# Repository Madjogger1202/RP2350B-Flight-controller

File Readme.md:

# RP2350B-Flight-controller  

> Ultra-compact flight controller for mini quadcopters, based on **RP2350B** MCU.  
> Board size: **30.5 × 39.8 mm**, yet includes IMU, radio module, motor drivers, and full USB power support.  

---

## Key Features  
- **MCU:** RP2350B (dual-core, PIO, USB device)  
- **IMU:** LSM6DS3 (accelerometer + gyroscope, SPI connection)  
- **Radio module:** NRF24L01 + RFX2401C PA/LNA amplifier  
- **Motors:** 4× brushed DC motors (up to 5 A per channel, short peak)  
- **USB-powered flight possible** (low-current motors, enough supply over USB)  
- **Additional expansion pins** (GPIO3–16 + SWD) for sensors, debugging, or add-ons  

---

## Pin Mapping  

### IMU (LSM6DS3) — SPI2  
| RP2350B GPIO | Signal | Notes |
|--------------|--------|-------|
| GPIO19 | SPI2_MISO | Sensor data out |
| GPIO22 | SPI2_MOSI | Sensor data in |
| GPIO23 | SPI2_SCK  | SPI clock |
| GPIO20 | IMU_INT1  | Interrupt 1 |
| GPIO21 | IMU_INT2  | Interrupt 2 |

---

### Radio Module (NRF24L01 + RFX2401C)  
| RP2350B GPIO | Signal | Notes |
|--------------|--------|-------|
| GPIO28 | SPI_MOSI | Shared SPI bus |
| GPIO36 | SPI_MISO | Shared SPI bus |
| GPIO37 | SPI_SCK  | Shared SPI bus |
| GPIO30 | NRF_CS   | Chip select |
| GPIO31 | NRF_CE   | Enable |
| GPIO32 | NRF_IRQ  | Interrupt |

---

### Motors  
| RP2350B GPIO | Output | Notes |
|--------------|--------|-------|
| GPIO45 | Motor_1 | Brushed motor driver |
| GPIO46 | Motor_2 | Brushed motor driver |
| GPIO47 | Motor_3 | Brushed motor driver |
| GPIO48 | Motor_4 | Brushed motor driver |
| GPIO49 | Motor_current | Current sense |
| GPIO52 | Motor_voltage | Battery/rail voltage sense |

---

### LEDs  
| RP2350B GPIO | Signal | Notes |
|--------------|--------|-------|
| GPIO17 | LED1 | Status LED |
| GPIO18 | LED2 | Status LED |

---

### Debug / Expansion  
- **SWD interface** exposed for programming/debugging  
- **GPIO3–16** free for custom extensions (I²C, UART, SPI, PWM, ADC etc.)  

---

## Power  
- Powered from **USB** or external battery  
- USB can sustain hover/low-thrust operation with small coreless motors  
- Onboard regulation for MCU, IMU, radio, and motor supply  

---

## Use Case  
- Designed for **tiny brushed quadcopters** and robotics experiments  
- Combines **motion sensing, wireless control, and motor drivers** in one small board  
- Fits into custom drone frames without extra breakout boards  

---

## Quick Start  
1. Connect via **USB-C** for firmware flashing and testing.  
2. Flash firmware (e.g. custom flight stack on RP2350B).  
3. Connect brushed motors to outputs GPIO45–48.  
4. Pair radio link via NRF24L01 (with RFX2401C amp).  
5. Power from USB for tests, or from LiPo for flight.  

---

## Notes  
- Motor channels rated for **5 A peak per motor** (coreless brushed).  
- Ensure airflow for heat dissipation at higher loads.  
- Expansion pins allow integration of GPS, barometer, or additional sensors.  

---

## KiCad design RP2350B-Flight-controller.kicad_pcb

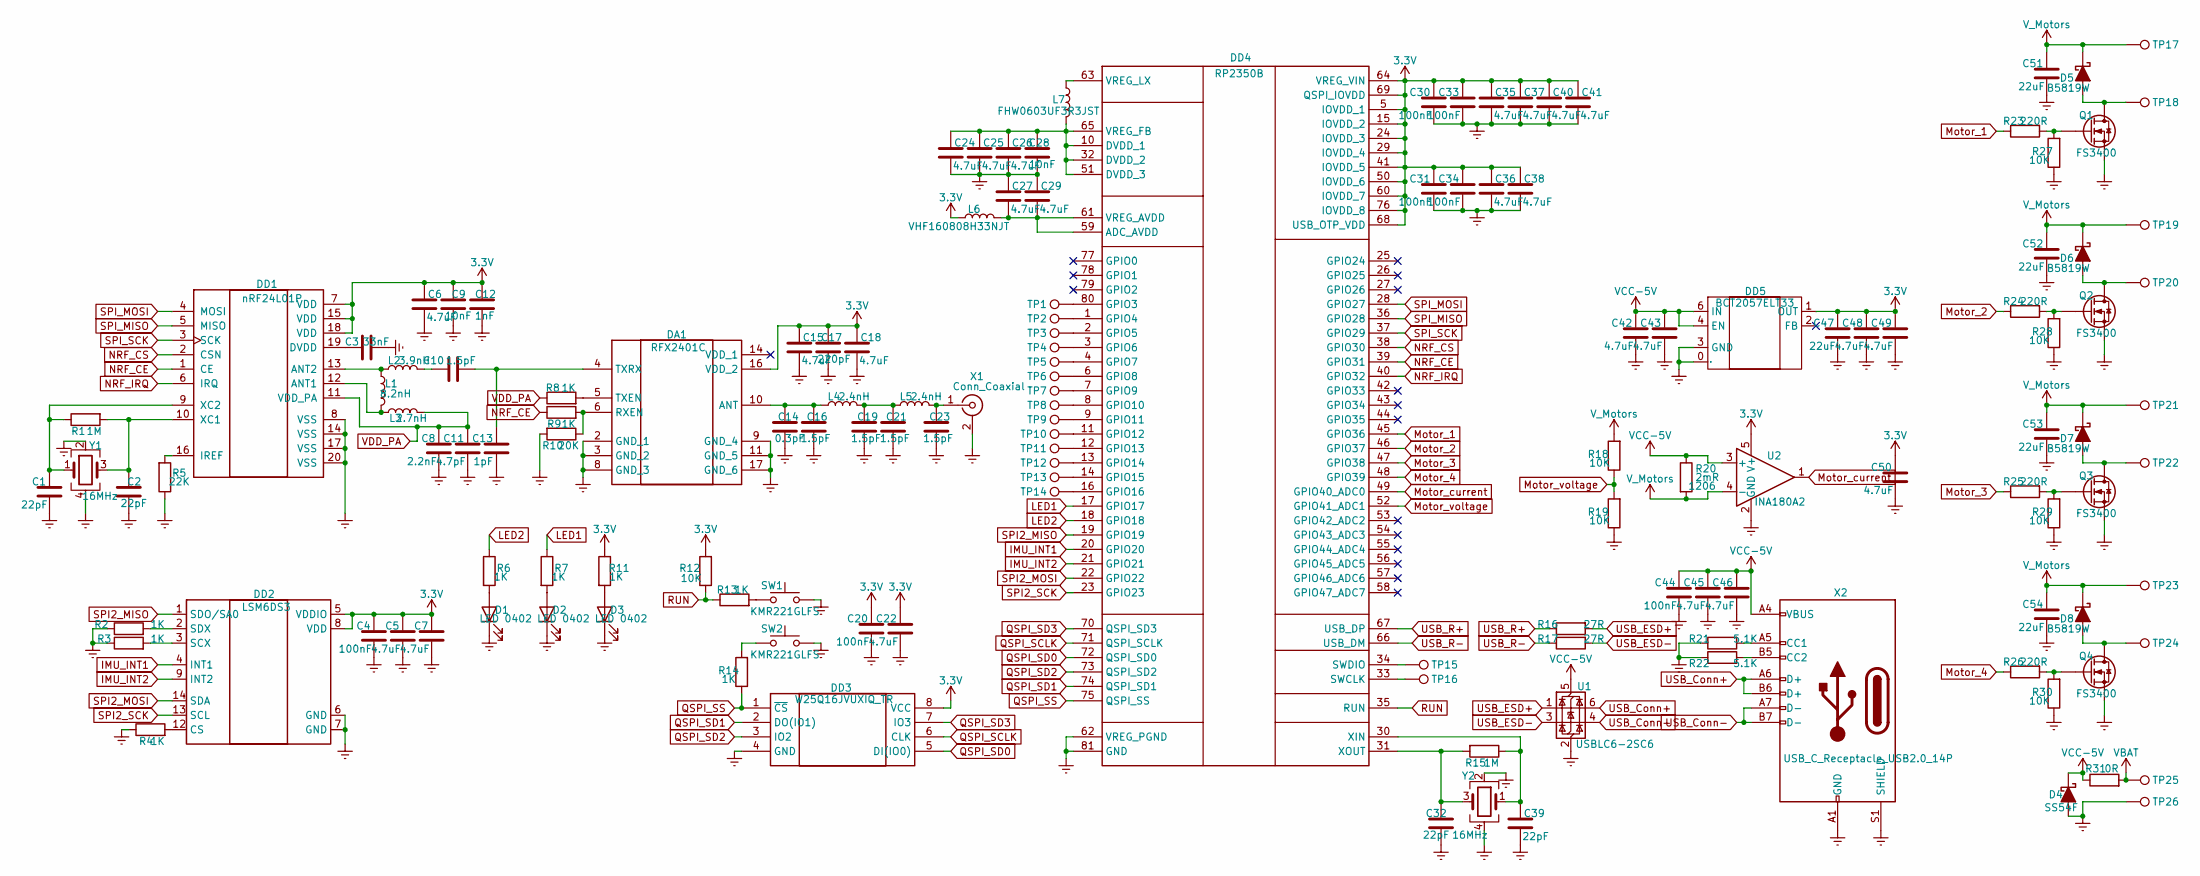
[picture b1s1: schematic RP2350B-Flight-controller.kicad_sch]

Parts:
C1, C2, C32, C39: 22pF; C_0201_0603Metric
C3: 33nF; C_0201_0603Metric
C4, C20, C30, C31, C33, C34, C44: 100nF; C_0201_0603Metric
C5, C6, C7, C15, C18, C22, C24, C25, C26, C27, C29, C35, C36, C37, C38, C40, C41, C42, C43, C45, C46, C48, C49, C50: 4.7uF; C_0201_0603Metric
C8: 2.2nF; C_0201_0603Metric
C9, C28: 10nF; C_0201_0603Metric
C10, C16, C19, C21, C23: 1.5pF; C_0201_0603Metric
C11: 4.7pF; C_0201_0603Metric
C12: 1nF; C_0201_0603Metric
C13: 1pF; C_0201_0603Metric
C14: 0.3pF; C_0201_0603Metric
C17: 220pF; C_0201_0603Metric
C47, C51, C52, C53, C54: 22uF; C_0402_1005Metric
D1, D2, D3: LED 0402; LED_0402_1005Metric
D4: SS54F; D_SMAFL
D5, D6, D7, D8: B5819W; D_SOD-123
DA1: RFX2401C; Manufacturer_Part_Number RFX2401C; Mouser Part Number 477-RFX2401C
DD1: nRF24L01P; QFN-20-1EP_4x4mm_P0.5mm_EP2.5x2.5mm
DD2: LSM6DS3; LGA-14_3x2.5mm_P0.5mm_LayoutBorder3x4y
DD3: W25Q16JVUXIQ_TR; W25Q16JVUXIQ; Manufacturer_Part_Number W25Q16JVUXIQ TR; Mouser Part Number 454-W25Q16JVUXIQTR
DD4: RP2350B; QFN40P1000X1000X90-81N-D; Manufacturer_Part_Number RP2350B
DD5: BCT2057ELT33; BCT2057ELTAJ; Manufacturer Part BCT2057ELTAJ-TR; LCSC Part Name 1A, 低 dropout 线性稳压器
L1: 8.2nH; L_0201_0603Metric
L2: 3.9nH; L_0201_0603Metric
L3: 2.7nH; L_0201_0603Metric
L4, L5: 2.4nH; L_0201_0603Metric
L6: VHF160808H33NJT; L_0603_1608Metric
L7: FHW0603UF3R3JST; L_0603_1608Metric
Q1, Q2, Q3, Q4: FS3400; SOT-23
R1, R15: 1M; R_0201_0603Metric
R2, R3, R4, R6, R7, R8, R9, R11, R13, R14: 1K; R_0201_0603Metric
R5: 22K; R_0201_0603Metric
R10: 20K; R_0201_0603Metric
R12, R18, R19, R27, R28, R29, R30: 10K; R_0201_0603Metric
R16, R17: 27R; R_0201_0603Metric
R20: 2mR; R_1206_3216Metric
R21, R22: 5.1K; R_0201_0603Metric
R23, R24, R25, R26: 220R; R_0201_0603Metric
R31: 0R; R_0805_2012Metric
SW1, SW2: KMR221GLFS; SW_SPST_PTS810
TP1, TP2, TP3, TP4, TP5, TP6, TP7, TP8, TP9, TP10, TP11, TP12, TP13, TP14, TP15, TP16: TestPoint; TestPoint_Pad_D1.0mm
TP17, TP18, TP19, TP20, TP21, TP22, TP23, TP24, TP25, TP26: TestPoint; TestPoint_Pad_D1.5mm
U1: USBLC6-2SC6; SOT-23-6
U2: INA180A2; SOT-23-5
X1: Conn_Coaxial; U.FL_Molex_MCRF_73412-0110_Vertical
X2: USB_C_Receptacle_USB2.0_14P; USB_C_Receptacle_GCT_USB4105-xx-A_16P_TopMnt_Horizontal
Y1, Y2: 16MHz; Crystal_SMD_3225-4Pin_3.2x2.5mm

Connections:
3.3V: C4.1, C5.1, C6.1, C7.1, C9.1, C12.1, C15.1, C17.1, C18.1, C20.1, C22.1, C30.1, C31.1, C33.1, C34.1, C35.1, C36.1, C37.1, C38.1, C40.1, C41.1, C47.1, C48.1, C49.1, C50.1, DA1.16 (VDD_2), DD1.7 (VDD), DD1.15 (VDD), DD1.18 (VDD), DD2.5 (VDDIO), DD2.8 (VDD), DD3.8 (VCC), DD4.5 (IOVDD_1), DD4.15 (IOVDD_2), DD4.24 (IOVDD_3), DD4.29 (IOVDD_4), DD4.41 (IOVDD_5), DD4.50 (IOVDD_6), DD4.60 (IOVDD_7), DD4.64 (VREG_VIN), DD4.68 (USB_OTP_VDD), DD4.69 (QSPI_IOVDD), DD4.76 (IOVDD_8), DD5.1 (OUT), L6.1, R11.1, R12.2, U2.5 (V+)
Earth: C1.2, C2.2, C3.2, C4.2, C5.2, C6.2, C7.2, C8.2, C9.2, C11.2, C12.2, C13.2, C14.2, C15.2, C16.2, C17.2, C18.2, C19.2, C20.2, C21.2, C22.2, C23.2, C24.2, C25.2, C26.2, C27.1, C28.2, C29.1, C30.2, C31.2, C32.2, C33.2, C34.2, C35.2, C36.2, C37.2, C38.2, C39.2, C40.2, C41.2, C42.2, C43.2, C44.2, C45.2, C46.2, C47.2, C48.2, C49.2, C50.2, C51.2, C52.2, C53.2, C54.2, D1.1 (K), D2.1 (K), D3.1 (K), D4.2 (A), DA1.2 (GND_1), DA1.3 (GND_2), DA1.8 (GND_3), DA1.9 (GND_4), DA1.11 (GND_5), DA1.17 (GND_6), DD1.8 (VSS), DD1.14 (VSS), DD1.17 (VSS), DD1.20 (VSS), DD1.21 (PAD), DD2.6 (GND), DD2.7 (GND), DD3.4 (GND), DD4.62 (VREG_PGND), DD4.81 (GND), DD5.0 (EP), DD5.3 (GND), Q1.2 (S), Q2.2 (S), Q3.2 (S), Q4.2 (S), R2.1, R3.1, R4.1, R5.1, R10.2, R19.1, R21.1, R22.1, R27.1, R28.1, R29.1, R30.1, SW1.1, SW2.1, TP26.1, U1.2 (GND), U2.2 (GND), X1.2 (Ext), X2.A1 (GND), X2.A12 (GND), X2.B1 (GND), X2.B12 (GND), X2.S1 (SHIELD), Y1.2, Y1.4, Y2.2, Y2.4
IMU_INT1: DD2.4 (INT1), DD4.20 (GPIO20)
IMU_INT2: DD2.9 (INT2), DD4.21 (GPIO21)
LED1: DD4.17 (GPIO17), R7.1
LED2: DD4.18 (GPIO18), R6.1
Motor_1: DD4.45 (GPIO36), R23.1
Motor_2: DD4.46 (GPIO37), R24.1
Motor_3: DD4.47 (GPIO38), R25.1
Motor_4: DD4.48 (GPIO39), R26.1
Motor_current: DD4.49 (GPIO40_ADC0), U2.1
Motor_voltage: DD4.52 (GPIO41_ADC1), R18.1, R19.2
NRF_CE: DD1.1 (CE), DD4.39 (GPIO31), R9.1
NRF_CS: DD1.2 (CSN), DD4.38 (GPIO30)
NRF_IRQ: DD1.6 (IRQ), DD4.40 (GPIO32)
unnamed: C10.1, L2.2
unnamed: C19.1, C21.1, L4.2, L5.1
unnamed: D1.2 (A), R6.2
unnamed: D2.2 (A), R7.2
unnamed: D3.2 (A), R11.2
unnamed: D5.2 (A), Q1.3 (D), TP18.1
unnamed: D6.2 (A), Q2.3 (D), TP20.1
unnamed: D7.2 (A), Q3.3 (D), TP22.1
unnamed: D8.2 (A), Q4.3 (D), TP24.1
unnamed: C14.1, C16.1, DA1.10 (ANT), L4.1
unnamed: DA1.6 (RXEN), R9.2, R10.1
unnamed: DA1.5 (TXEN), R8.2
unnamed: C10.2, C13.1, DA1.4 (TXRX)
unnamed: DD1.12 (ANT1), L1.2, L3.1
unnamed: DD1.13 (ANT2), L1.1, L2.1
unnamed: C3.1, DD1.19 (DVDD)
unnamed: DD1.16 (IREF), R5.2
unnamed: C2.1, DD1.10 (XC1), R1.2, Y1.3
unnamed: C1.1, DD1.9 (XC2), R1.1, Y1.1
unnamed: DD2.12 (CS), R4.2
unnamed: DD2.3 (SCX), R3.2
unnamed: DD2.2 (SDX), R2.2
unnamed: C27.2, C29.2, DD4.59 (ADC_AVDD), DD4.61 (VREG_AVDD), L6.2
unnamed: C24.1, C25.1, C26.1, C28.1, DD4.10 (DVDD_1), DD4.32 (DVDD_2), DD4.51 (DVDD_3), DD4.65 (VREG_FB), L7.2
unnamed: DD4.80 (GPIO3), TP1.1
unnamed: DD4.1 (GPIO4), TP2.1
unnamed: DD4.2 (GPIO5), TP3.1
unnamed: DD4.3 (GPIO6), TP4.1
unnamed: DD4.4 (GPIO7), TP5.1
unnamed: DD4.6 (GPIO8), TP6.1
unnamed: DD4.7 (GPIO9), TP7.1
unnamed: DD4.8 (GPIO10), TP8.1
unnamed: DD4.9 (GPIO11), TP9.1
unnamed: DD4.11 (GPIO12), TP10.1
unnamed: DD4.12 (GPIO13), TP11.1
unnamed: DD4.13 (GPIO14), TP12.1
unnamed: DD4.14 (GPIO15), TP13.1
unnamed: DD4.16 (GPIO16), TP14.1
unnamed: DD4.33 (SWCLK), TP16.1
unnamed: DD4.34 (SWDIO), TP15.1
unnamed: DD4.63 (VREG_LX), L7.1
unnamed: C39.1, DD4.30 (XIN), R15.1, Y2.1
unnamed: C32.1, DD4.31 (XOUT), R15.2, Y2.3
unnamed: Q1.1 (G), R23.2, R27.2
unnamed: Q2.1 (G), R24.2, R28.2
unnamed: Q3.1 (G), R25.2, R29.2
unnamed: Q4.1 (G), R26.2, R30.2
unnamed: R13.2, SW1.2
unnamed: R14.2, SW2.2
unnamed: C23.1, L5.2, X1.1 (In)
unnamed: R21.2, X2.A5 (CC1)
unnamed: R22.2, X2.B5 (CC2)
QSPI_SCLK: DD3.6 (CLK), DD4.71 (QSPI_SCLK)
QSPI_SD0: DD3.5 (DI(IO0)), DD4.72 (QSPI_SD0)
QSPI_SD1: DD3.2 (DO(IO1)), DD4.74 (QSPI_SD1)
QSPI_SD2: DD3.3 (IO2), DD4.73 (QSPI_SD2)
QSPI_SD3: DD3.7 (IO3), DD4.70 (QSPI_SD3)
QSPI_SS: DD3.1 (~CS), DD4.75 (QSPI_SS), R14.1
RUN: DD4.35 (RUN), R12.1, R13.1
SPI2_MISO: DD2.1 (SDO/SA0), DD4.19 (GPIO19)
SPI2_MOSI: DD2.14 (SDA), DD4.22 (GPIO22)
SPI2_SCK: DD2.13 (SCL), DD4.23 (GPIO23)
SPI_MISO: DD1.5 (MISO), DD4.36 (GPIO28)
SPI_MOSI: DD1.4 (MOSI), DD4.28 (GPIO27)
SPI_SCK: DD1.3 (SCK), DD4.37 (GPIO29)
USB_Conn+: U1.6 (I/O1), X2.A6 (D+), X2.B6 (D+)
USB_Conn-: U1.4 (I/O2), X2.A7 (D-), X2.B7 (D-)
USB_ESD+: R16.2, U1.1 (I/O1)
USB_ESD-: R17.2, U1.3 (I/O2)
USB_R+: DD4.67 (USB_DP), R16.1
USB_R-: DD4.66 (USB_DM), R17.1
VBAT: R31.2, TP25.1
VCC-5V: C42.1, C43.1, C44.1, C45.1, C46.1, D4.1 (K), DD5.4 (EN), DD5.6 (IN), R20.1, R31.1, U1.5 (VBUS), U2.3 (+), X2.A4 (VBUS), X2.A9 (VBUS), X2.B4 (VBUS), X2.B9 (VBUS)
VDD_PA: C8.1, C11.1, DD1.11 (VDD_PA), L3.2, R8.1
V_Motors: C51.1, C52.1, C53.1, C54.1, D5.1 (K), D6.1 (K), D7.1 (K), D8.1 (K), R18.2, R20.2, TP17.1, TP19.1, TP21.1, TP23.1, U2.4 (-)

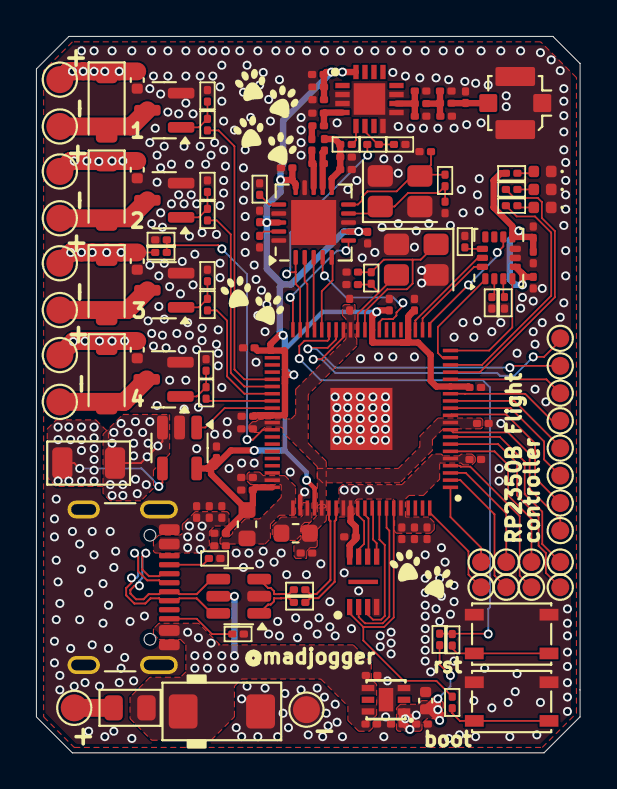
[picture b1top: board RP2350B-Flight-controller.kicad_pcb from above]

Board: 2 copper layers, 30.2 x 39.8 mm, 144 parts (0 on the bottom side), 90 nets.

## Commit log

2025-09-04 started schematics
2025-09-06 schematics and component placement done
2025-09-06 rev0 ready
2025-09-07 connected 21 pin of nrf24l01+ to GND
